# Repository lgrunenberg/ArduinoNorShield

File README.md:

# ArduinoNorShield

A quick and dirty Arduino shield that can - but should not - be used for connecting Nor-Flash memory chips to Arduino boards running at 3.3 Volts and following the Arduino Mega pinout specifications, e.g. the Arduino Due.

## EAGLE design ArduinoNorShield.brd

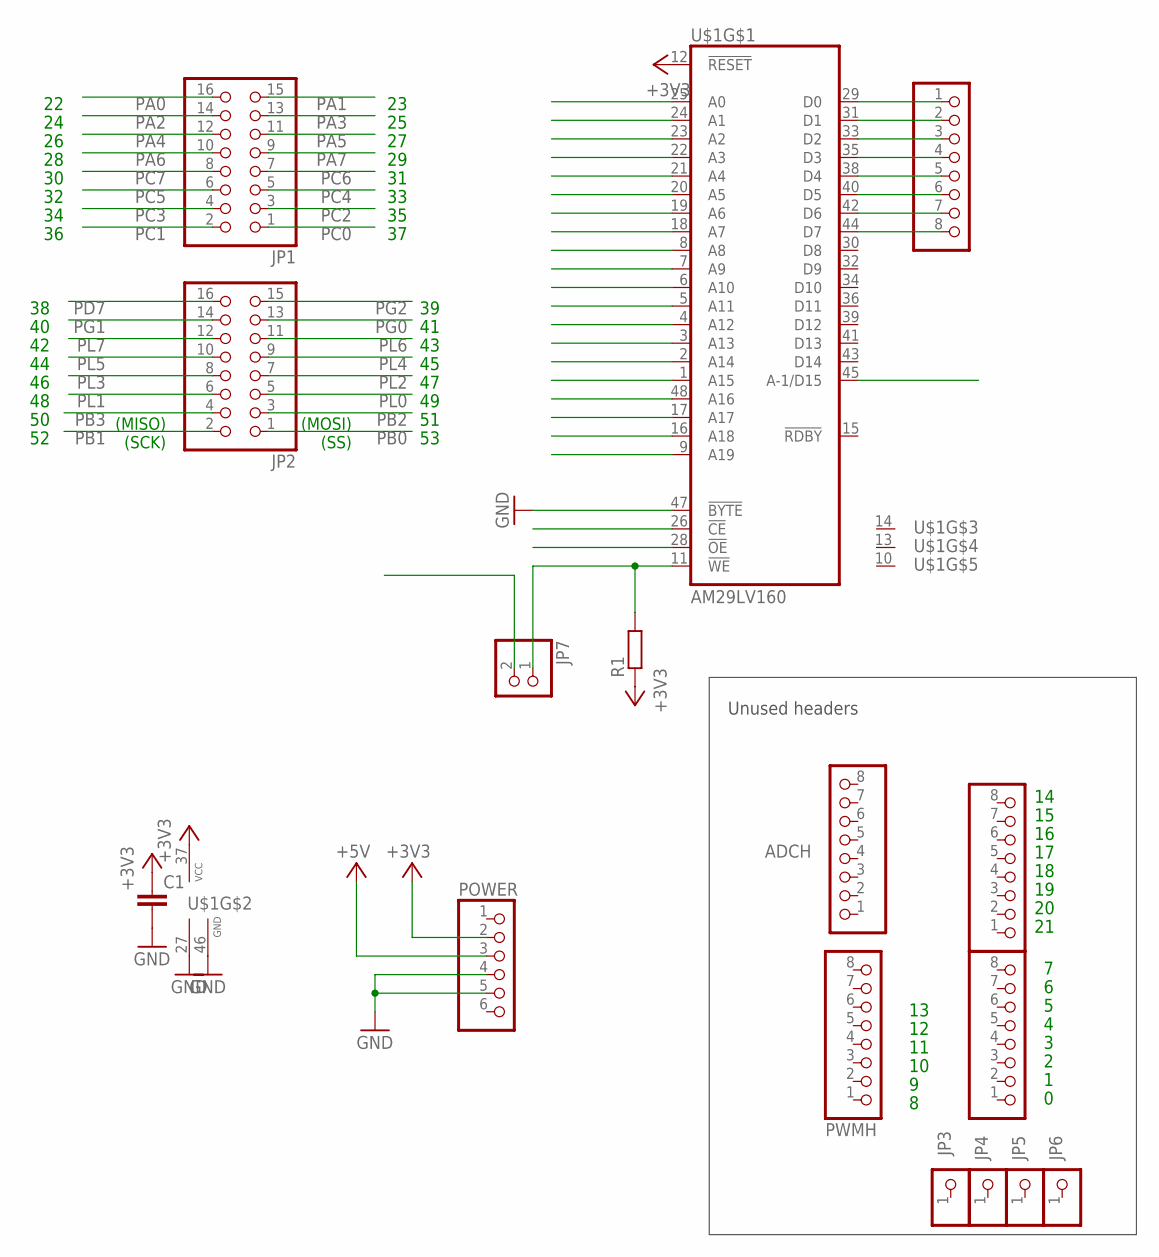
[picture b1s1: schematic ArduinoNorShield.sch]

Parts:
ADCH: PINHD-1X8; 1X08
ADCL: PINHD-1X8; 1X08
C1: C-EUC0805; C0805
COMMUNICATION: PINHD-1X8; 1X08
JP1, JP2: PINHD-2X8; 2X08
JP3, JP4, JP5, JP6: PINHD-1X1; 1X01
JP7: PINHD-1X2; 1X02
POWER: PINHD-1X6; 1X06
PWMH: PINHD-1X8; 1X08
PWML: PINHD-1X8; 1X08
R1: R-EU_R0805; R0805
U$1: AM29LV160; TSOP48

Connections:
+3V3: C1.1, POWER.2, R1.1, U$1.12 (!RESET), U$1.37 (VCC)
+5V: POWER.3
GND: C1.2, POWER.4, POWER.5, U$1.27 (GND), U$1.46 (GND), U$1.47 (!BYTE)
unnamed: ADCL.1, U$1.29 (D0)
unnamed: ADCL.2, U$1.31 (D1)
unnamed: ADCL.3, U$1.33 (D2)
unnamed: ADCL.4, U$1.35 (D3)
unnamed: ADCL.5, U$1.38 (D4)
unnamed: ADCL.6, U$1.40 (D5)
unnamed: ADCL.7, U$1.42 (D6)
unnamed: ADCL.8, U$1.44 (D7)
unnamed: JP7.1, R1.2, U$1.11 (!WE)
PA0: JP1.16, U$1.45 (A-1/D15)
PA1: JP1.15, U$1.25 (A0)
PA2: JP1.14, U$1.24 (A1)
PA3: JP1.13, U$1.23 (A2)
PA4: JP1.12, U$1.22 (A3)
PA5: JP1.11, U$1.21 (A4)
PA6: JP1.10, U$1.20 (A5)
PA7: JP1.9, U$1.19 (A6)
PB0: JP2.1
PB1: JP2.2
PB2: JP2.3
PB3: JP2.4
PC0: JP1.1, U$1.2 (A14)
PC1: JP1.2, U$1.3 (A13)
PC2: JP1.3, U$1.4 (A12)
PC3: JP1.4, U$1.5 (A11)
PC4: JP1.5, U$1.6 (A10)
PC5: JP1.6, U$1.7 (A9)
PC6: JP1.7, U$1.8 (A8)
PC7: JP1.8, U$1.18 (A7)
PD7: JP2.16, U$1.1 (A15)
PG0: JP2.13, U$1.16 (A18)
PG1: JP2.14, U$1.17 (A17)
PG2: JP2.15, U$1.48 (A16)
PL0: JP2.5
PL1: JP2.6
PL2: JP2.7
PL3: JP2.8
PL4: JP2.9, U$1.28 (!OE)
PL5: JP2.10, U$1.26 (!CE)
PL6: JP2.11, JP7.2
PL7: JP2.12, U$1.9 (A19)

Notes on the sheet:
(SS)
(MOSI)
(SCK)
(MISO)
Unused headers

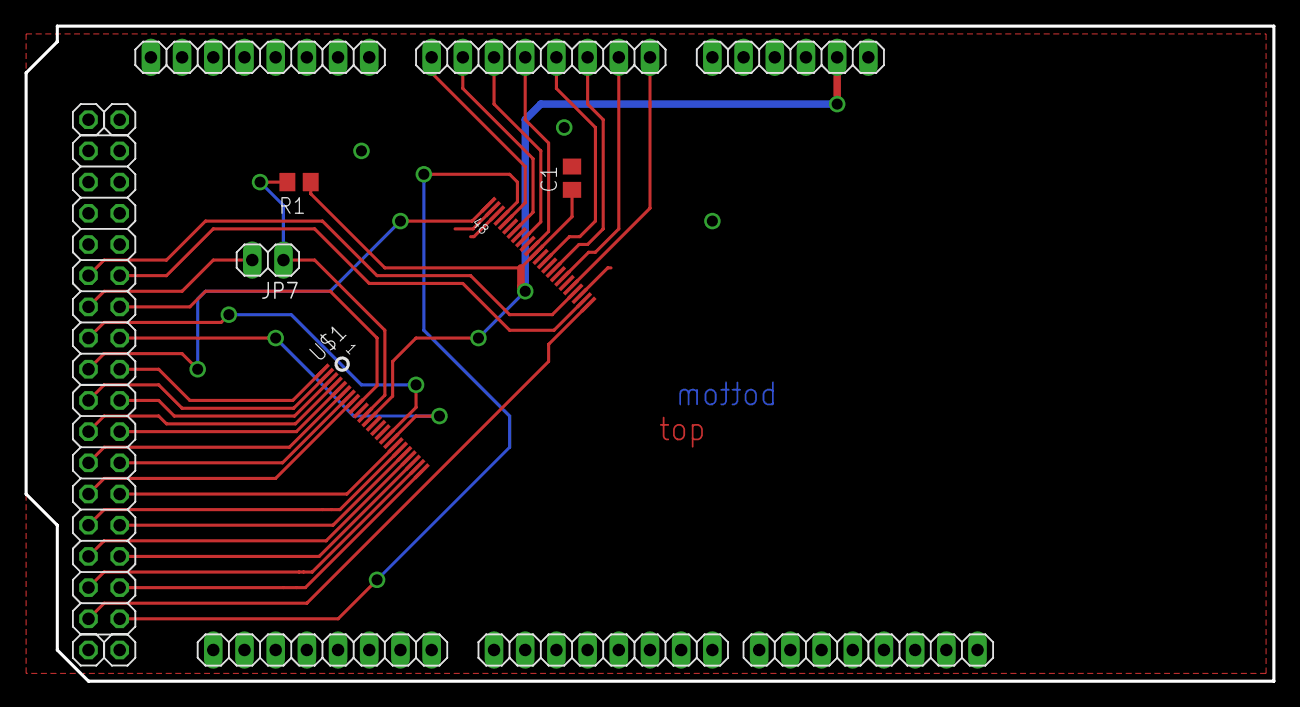
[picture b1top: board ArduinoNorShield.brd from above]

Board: 2 copper layers, 101.6 x 53.3 mm, 16 parts (0 on the bottom side), 35 nets.
